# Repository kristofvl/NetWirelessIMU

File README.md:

# Networked Wireless IMUs

A project started by Frederic Philips as a Masters thesis, now continued to update a hardware/software system of networked IMUs.

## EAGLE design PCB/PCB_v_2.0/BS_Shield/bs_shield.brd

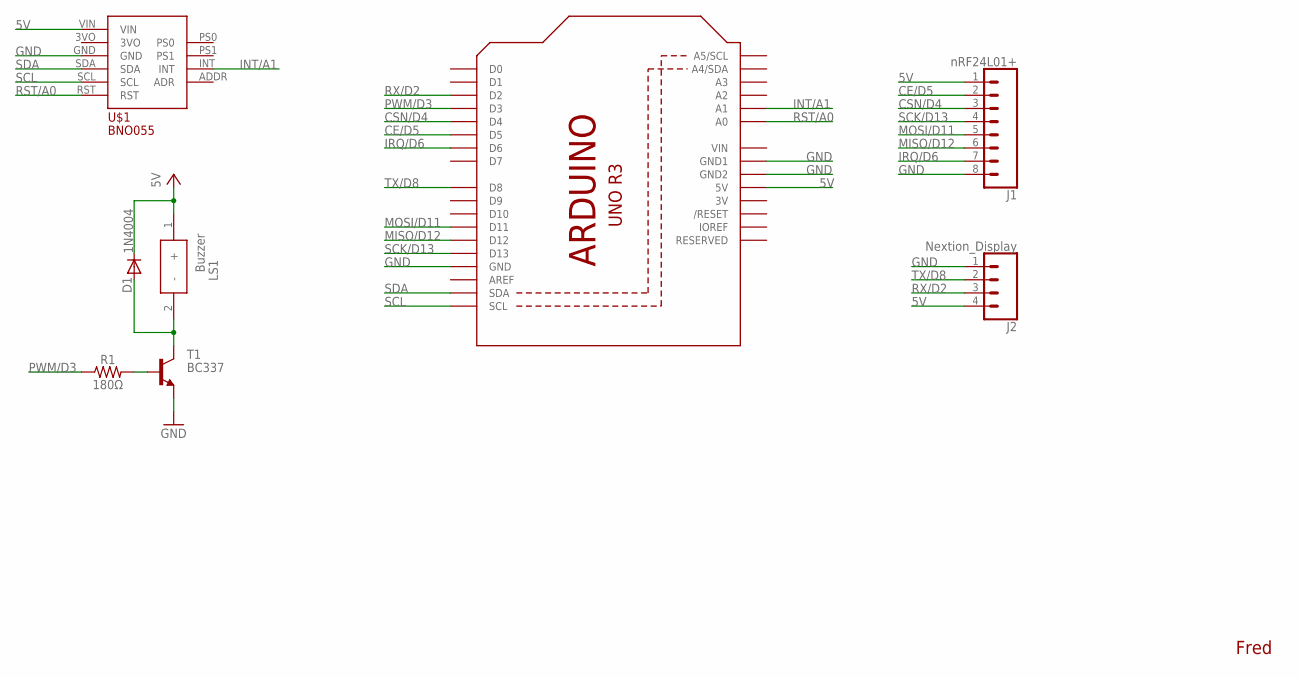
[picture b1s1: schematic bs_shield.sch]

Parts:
D1: 1N4004; DO41-10
J1: nRF24L01+; 1X08
J2: Nextion_Display; 1X04
LS1: Buzzer; CEM-1203(42)
R1: 180Ω; AXIAL-0.3
T1: BC337; TO92
U1: ARDUINOR3-DIMENSION; ARDUINOR3
U$1: BNO055; BB10

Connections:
3V: U1.3V
5V: D1.C, J1.1, J2.4, LS1.1 (+), U1.5V, U$1.VIN
CE/D5: J1.2, U1.D5
CSN/D4: J1.3, U1.D4
GND: J1.8, J2.1, T1.1 (E), U1.GND, U1.GND1, U1.GND2, U$1.GND
INT/A1: U1.A1, U$1.INT
IRQ/D6: J1.7, U1.D6
MISO/D12: J1.6, U1.D12
MOSI/D11: J1.5, U1.D11
unnamed: R1.P$2 (2), T1.2 (B)
unnamed: D1.A, LS1.2 (-), T1.3 (C)
PWM/D3: R1.P$1 (1), U1.D3
RST/A0: U1.A0, U$1.RST
RX/D2: J2.3, U1.D2
SCK/D13: J1.4, U1.D13
SCL: U1.SCL, U$1.SCL
SDA: U1.SDA, U$1.SDA
TX/D8: J2.2, U1.D8
VIN: U1.VIN

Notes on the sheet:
Fred

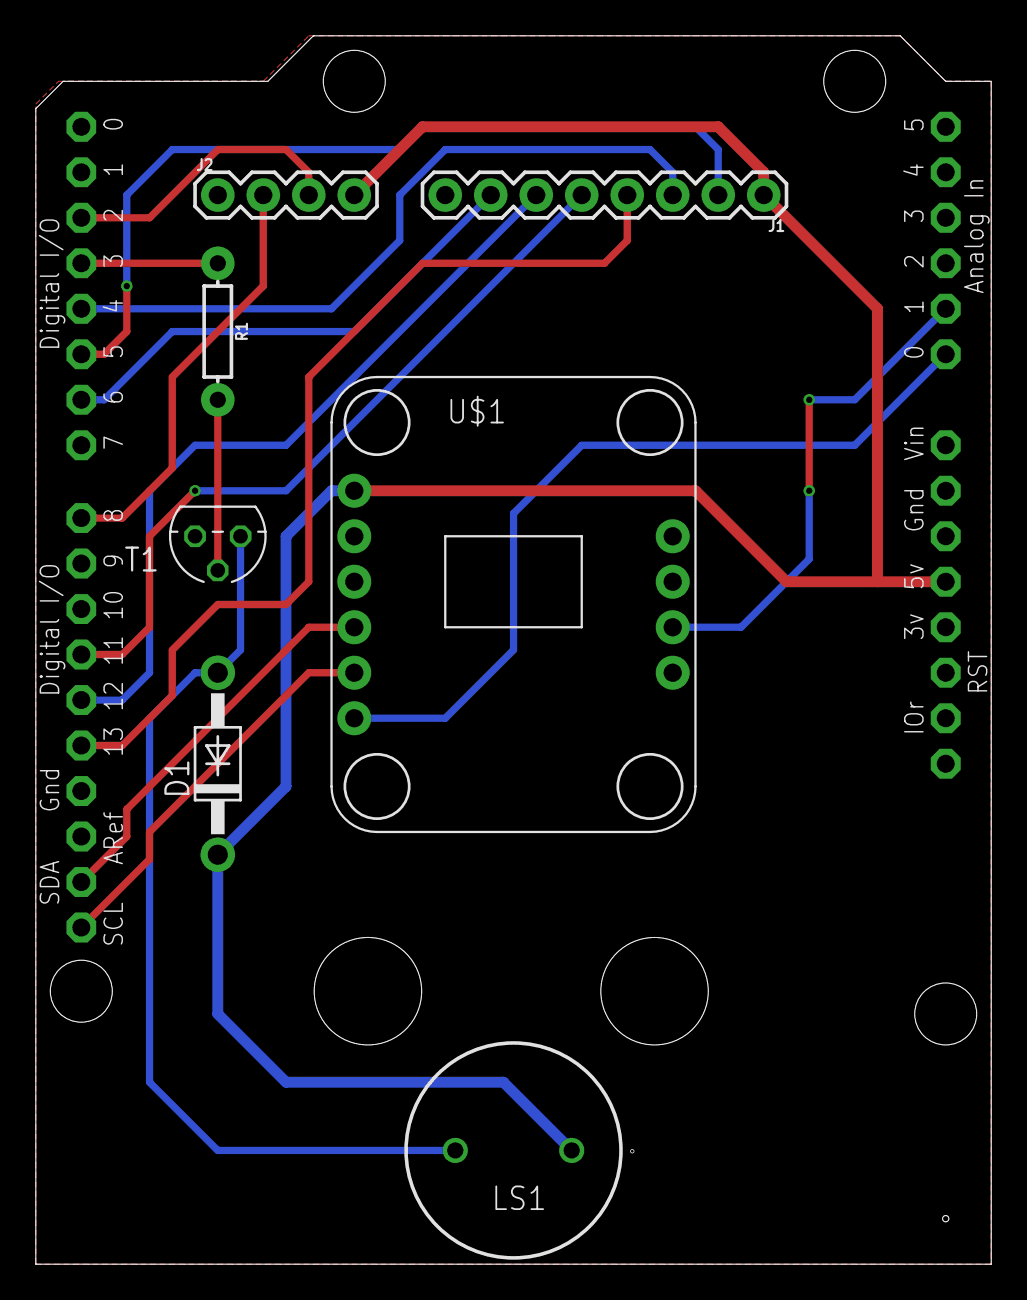
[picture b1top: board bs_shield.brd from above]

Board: 2 copper layers, 53.3 x 68.6 mm, 8 parts (0 on the bottom side), 17 nets.

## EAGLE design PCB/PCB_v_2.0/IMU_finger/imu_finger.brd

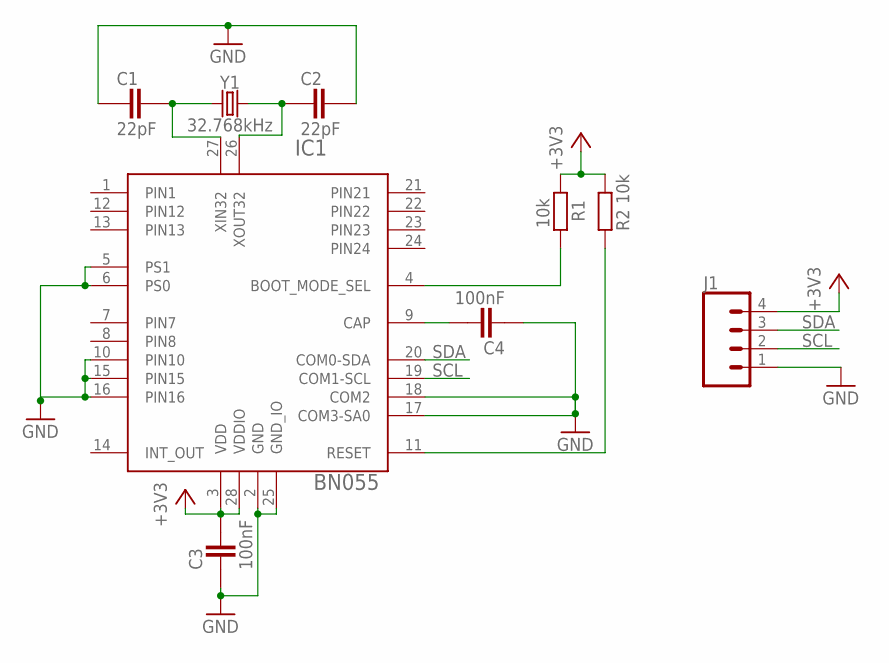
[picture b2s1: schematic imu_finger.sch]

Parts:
C1, C2: 22pF; CAPC1608X92N
C3, C4: 100nF; CAPC1608X92N
IC1: BN055; LGA-28_3.80X5.20/0.5
J1: CONN_04SMD2; 1X04_1MM_RA
R1, R2: 10k; RESC1608X55N
Y1: 32.768kHz; CRYSTAL-SMD-3.2X1.5MM

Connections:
+3V3: C3.2, IC1.3 (VDD), IC1.28 (VDDIO), J1.4, R1.1, R2.1
GND: C1.1, C2.2, C3.1, C4.1, IC1.2 (GND), IC1.5 (PS1), IC1.6 (PS0), IC1.10 (PIN10), IC1.15 (PIN15), IC1.16 (PIN16), IC1.17 (COM3-SA0), IC1.18 (COM2), IC1.25 (GND_IO), J1.1
unnamed: IC1.11 (RESET), R2.2
unnamed: IC1.4 (BOOT_MODE_SEL), R1.2
unnamed: C4.2, IC1.9 (CAP)
unnamed: C2.1, IC1.26 (XOUT32), Y1.P$2 (2)
unnamed: C1.2, IC1.27 (XIN32), Y1.P$1 (1)
SCL: IC1.19 (COM1-SCL), J1.2
SDA: IC1.20 (COM0-SDA), J1.3

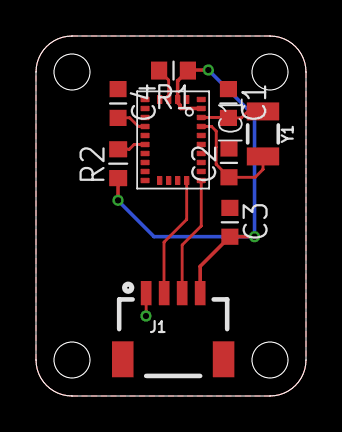
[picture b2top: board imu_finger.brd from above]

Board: 2 copper layers, 15.0 x 20.0 mm, 9 parts (0 on the bottom side), 9 nets.

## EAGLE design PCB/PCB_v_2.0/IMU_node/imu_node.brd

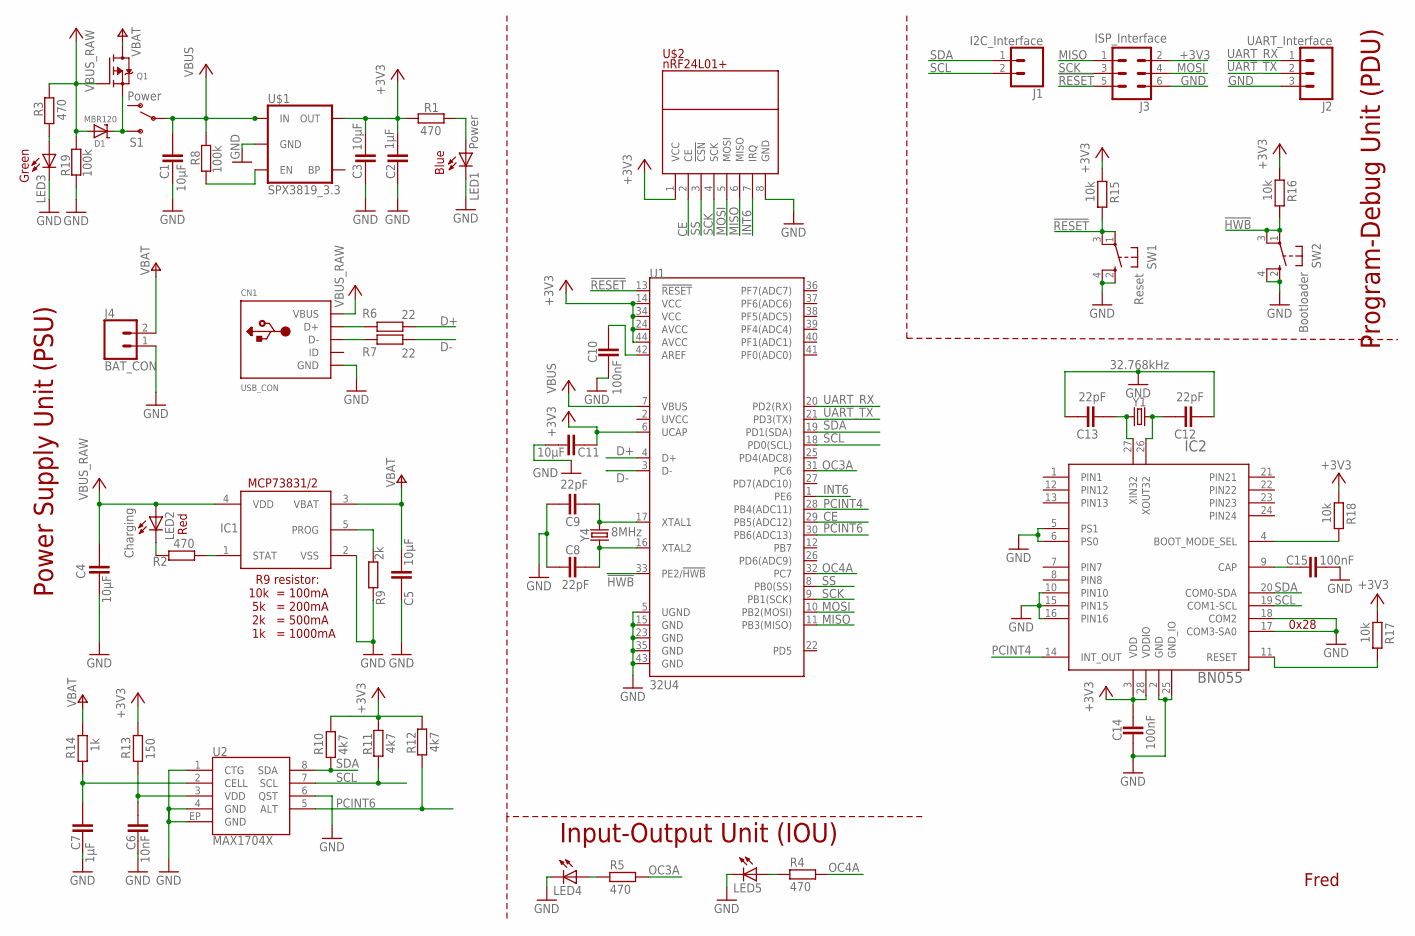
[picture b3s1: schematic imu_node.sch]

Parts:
C1, C3, C4, C5, C11: 10µF; CAPC1608X92N
C2, C7: 1µF; CAPC1608X92N
C6: 10nF; CAPC1608X92N
C8, C9, C12, C13: 22pF; CAPC1608X92N
C10, C14, C15: 100nF; CAPC1608X92N
CN1: USB_CON; USB-MINIB
D1: MBR120; SOD-123FL
IC1: MCP73831/OT; SOT23-5L
IC2: BN055; LGA-28_3.80X5.20/0.5
J1: I2C_Interface; 1X02
J2: UART_Interface; 1X03
J3: ISP_Interface; 2X3
J4: BAT_CON; 1X02
LED1: Power; CHIPLED_0603
LED2: Charging; CHIPLED_0603
LED3: USB; CHIPLED_0603
LED4, LED5: LEDCHIPLED_0603; CHIPLED_0603
Q1: MICROBUILDER_MOSFET-P; MICROBUILDER_SOT23-R
R1, R2, R3, R4, R5: 470; RESC1608X55N
R6, R7: 22; RESC1608X55N
R8, R19: 100k; RESC1608X55N
R9: 2k; RESC1608X55N
R10, R11, R12: 4k7; RESC1608X55N
R13: 150; RESC1608X55N
R14: 1k; RESC1608X55N
R15, R16, R17, R18: 10k; RESC1608X55N
S1: Power; SWITCH_SPST_SMD_A
SW1: Reset; KMR2
SW2: Bootloader; KMR2
U1: 32U4; TQFP44
U2: MAX1704X; TDFN-8
U$1: SPX3819_3.3; SOT23-5
U$2: nRF24L01+; 6-PIN-BREAKOUT
Y1: 32.768kHz; CRYSTAL-SMD-3.2X1.5MM
Y4: 8MHz; CRYSTAL-SMD-5X3.2-4PAD

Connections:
!HWB!: R16.2, SW2.1, SW2.3 (P1), U1.33 (PE2/!HWB)
!RESET!: J3.5, R15.2, SW1.1, SW1.3 (P1), U1.13 (!RESET)
+3V3: C2.2, C3.2, C11.1, C14.1, IC2.3 (VDD), IC2.28 (VDDIO), J3.2, R1.2, R10.1, R11.1, R12.1, R13.1, R15.1, R16.1, R17.1, R18.1, U1.6 (UCAP), U1.14 (VCC), U1.24 (AVCC), U1.34 (VCC), U1.44 (AVCC), U$1.5 (OUT), U$2.1 (VCC)
CE: U1.29 (PB5(ADC12)), U$2.2 (CE)
D+: R6.1, U1.4 (D+)
D-: R7.1, U1.3 (D-)
GND: C1.1, C2.1, C3.1, C4.1, C5.1, C6.1, C7.1, C8.2, C9.2, C10.2, C11.2, C12.1, C13.2, C14.2, C15.2, CN1.GND, IC1.2 (VSS), IC2.2 (GND), IC2.5 (PS1), IC2.6 (PS0), IC2.10 (PIN10), IC2.15 (PIN15), IC2.16 (PIN16), IC2.17 (COM3-SA0), IC2.18 (COM2), IC2.25 (GND_IO), J2.3, J3.6, J4.1, LED1.C, LED3.C, LED4.C, LED5.C, R9.2, R19.2, SW1.2 (S), SW1.4 (S1), SW2.2 (S), SW2.4 (S1), U1.5 (UGND), U1.15 (GND), U1.23 (GND), U1.35 (GND), U1.43 (GND), U2.1 (CTG), U2.4 (GND), U2.6 (QST), U2.EP (GND), U$1.2 (GND), U$2.8 (GND)
INT6: U1.1 (PE6), U$2.7 (IRQ)
MISO: J3.1, U1.11 (PB3(MISO)), U$2.6 (MISO)
MOSI: J3.4, U1.10 (PB2(MOSI)), U$2.5 (MOSI)
unnamed: CN1.D+, R6.2
unnamed: CN1.D-, R7.2
unnamed: IC1.5 (PROG), R9.1
unnamed: LED2.C, R2.2
unnamed: R8.2, U$1.3 (EN)
unnamed: C13.1, IC2.27 (XIN32), Y1.P$1 (1)
unnamed: LED1.A, R1.1
unnamed: IC1.1 (STAT), R2.1
unnamed: LED3.A, R3.2
unnamed: C9.1, U1.17 (XTAL1), Y4.3 (2)
unnamed: C8.1, U1.16 (XTAL2), Y4.1
unnamed: C10.1, U1.42 (AREF)
unnamed: C6.2, R13.2, U2.3 (VDD)
unnamed: C7.2, R14.2, U2.2 (CELL)
unnamed: LED4.A, R5.1
unnamed: C12.2, IC2.26 (XOUT32), Y1.P$2 (2)
unnamed: LED5.A, R4.1
unnamed: D1.C, Q1.2 (S), S1.3 (S)
unnamed: IC2.11 (RESET), R17.2
unnamed: C15.1, IC2.9 (CAP)
unnamed: IC2.4 (BOOT_MODE_SEL), R18.2
OC3A: R5.2, U1.31 (PC6)
OC4A: R4.2, U1.32 (PC7)
PCINT4: IC2.14 (INT_OUT), U1.28 (PB4(ADC11))
PCINT6: R12.2, U1.30 (PB6(ADC13)), U2.5 (ALT)
SCK: J3.3, U1.9 (PB1(SCK)), U$2.4 (SCK)
SCL: IC2.19 (COM1-SCL), J1.2, R11.2, U1.18 (PD0(SCL)), U2.7 (SCL)
SDA: IC2.20 (COM0-SDA), J1.1, R10.2, U1.19 (PD1(SDA)), U2.8 (SDA)
SS: U1.8 (PB0(SS)), U$2.3 (!CSN!)
UART_RX: J2.1, U1.20 (PD2(RX))
UART_TX: J2.2, U1.21 (PD3(TX))
VBAT: C5.2, IC1.3 (VBAT), J4.2, Q1.3 (D), R14.1
VBUS: C1.2, R8.1, S1.2, U1.7 (VBUS), U$1.1 (IN)
VBUS_RAW: C4.2, CN1.VBUS, D1.A, IC1.4 (VDD), LED2.A, Q1.1 (G), R3.1, R19.1

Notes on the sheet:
Power Supply Unit (PSU)
Blue
Red
Green
R9 resistor: 10k = 100mA 5k = 200mA 2k = 500mA 1k = 1000mA
nRF24L01+
Program-Debug Unit (PDU)
Input-Output Unit (IOU)
0x28
Fred

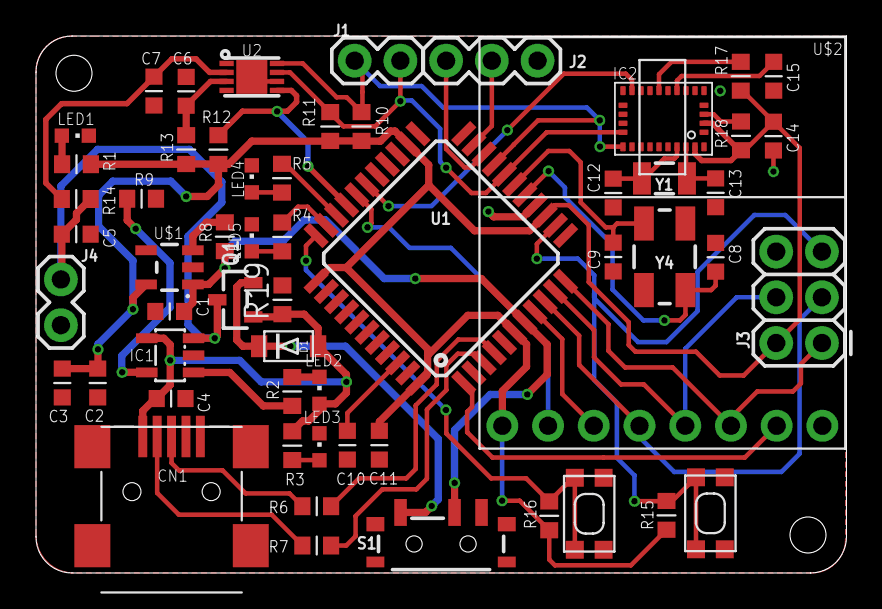
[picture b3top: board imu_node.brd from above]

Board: 2 copper layers, 45.0 x 29.8 mm, 57 parts (0 on the bottom side), 44 nets.

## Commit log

2017-12-11 Time in milliseconds linux C code added
    Uses clock_gettime function
2017-12-11 Change funtion to main
2017-12-11 Added timeinms executable
2017-12-11 Create UDP
2017-12-11 client.c for UDP added
2017-12-11 Added server.c file for UDP
2017-12-11 added code to client.c
2017-12-11 added code for server.c
2017-12-11 New client code
2017-12-11 New server code
2017-12-11 removed gets
2017-12-11 Added line 50 to clean buffer
2017-12-17 Updated timestamp code
2017-12-17 Removed POSIX macro
2018-05-15 AVR Blinky, Adc & UART test codes
2018-06-01 Restructured file paths and added Test_BNO055 AVR Project
2018-06-12 Corrected logical error in setting RX pin as input
2018-06-19 Initial commit of Test_nRF24L01
2018-06-19 Changed the tab and indent size of all files from 4 to 8 to match Github's
2018-06-19 Added reference folder with nRF_Config flowchart
2018-06-20 Added registers and bits' info to nRF_Config flowchart
2018-06-20 Added flowchart for nRF test
2018-06-29 Updated nRF_Config() function in RX
2018-07-04 Updated the first version of nRF RX test
2018-07-04 Updated the first version of nRF TX test
2018-08-24 Added PCB Reference files
2018-08-24 Many test firmware files added and updated
2018-08-29 Added block diagrams for IMU and eGlove PCBs
2018-09-07 Added IMU_node PCB design files
2018-09-11 Added latest version of IMU node PCB
2018-09-14 Added the first version of IMU_node, IMU_finger & IMU_hand PCBs
2018-09-14 Updated PCB_TODO
2018-11-23 Major Firmware update
2019-04-10 Added Nextion Display HMI files
2019-04-10 Uploaded more reference documents
2019-04-10 Added the final AVR firmware files
2019-04-10 Added latest PCB files and BOM
2019-04-10 Added Nucleo files
2019-04-10 Removed redundant time_ms.c file
2019-04-10 Added Nextion images and fonts
2020-08-28 Updated code base
    New, optimized code; do not use old code anymore
2020-11-25 Added LED blinking for finger tip debugging
2020-11-25 Python code to read glove and store data
2025-05-15 reorganised directories to avoid duplication

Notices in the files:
parts and their libraries:
SparkFun-IC-Microcontroller: Licensing: Creative Commons ShareAlike 4.0 International - https://creativecommons.org/licenses/by-sa/4.0
